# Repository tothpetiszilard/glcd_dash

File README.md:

# glcd_dash
Very old (2015) project - T6963 based GLCD dashboard for a motorcycle

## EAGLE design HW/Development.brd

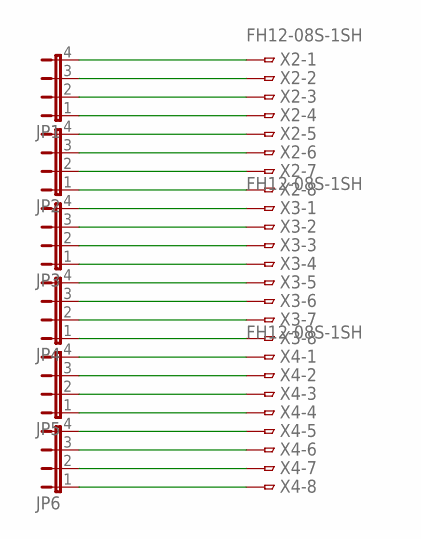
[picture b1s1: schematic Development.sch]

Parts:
JP1, JP2, JP3, JP4, JP5, JP6: JP4E; JP4
X2, X3, X4: FH12-08S-1SH

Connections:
unnamed: JP1.4, X2.1
unnamed: JP1.3, X2.2
unnamed: JP1.2, X2.3
unnamed: JP1.1, X2.4
unnamed: JP2.4, X2.5
unnamed: JP2.3, X2.6
unnamed: JP2.2, X2.7
unnamed: JP2.1, X2.8
unnamed: JP3.4, X3.1
unnamed: JP3.3, X3.2
unnamed: JP3.2, X3.3
unnamed: JP3.1, X3.4
unnamed: JP4.4, X3.5
unnamed: JP4.3, X3.6
unnamed: JP4.2, X3.7
unnamed: JP4.1, X3.8
unnamed: JP5.4, X4.1
unnamed: JP5.3, X4.2
unnamed: JP5.2, X4.3
unnamed: JP5.1, X4.4
unnamed: JP6.4, X4.5
unnamed: JP6.3, X4.6
unnamed: JP6.2, X4.7
unnamed: JP6.1, X4.8

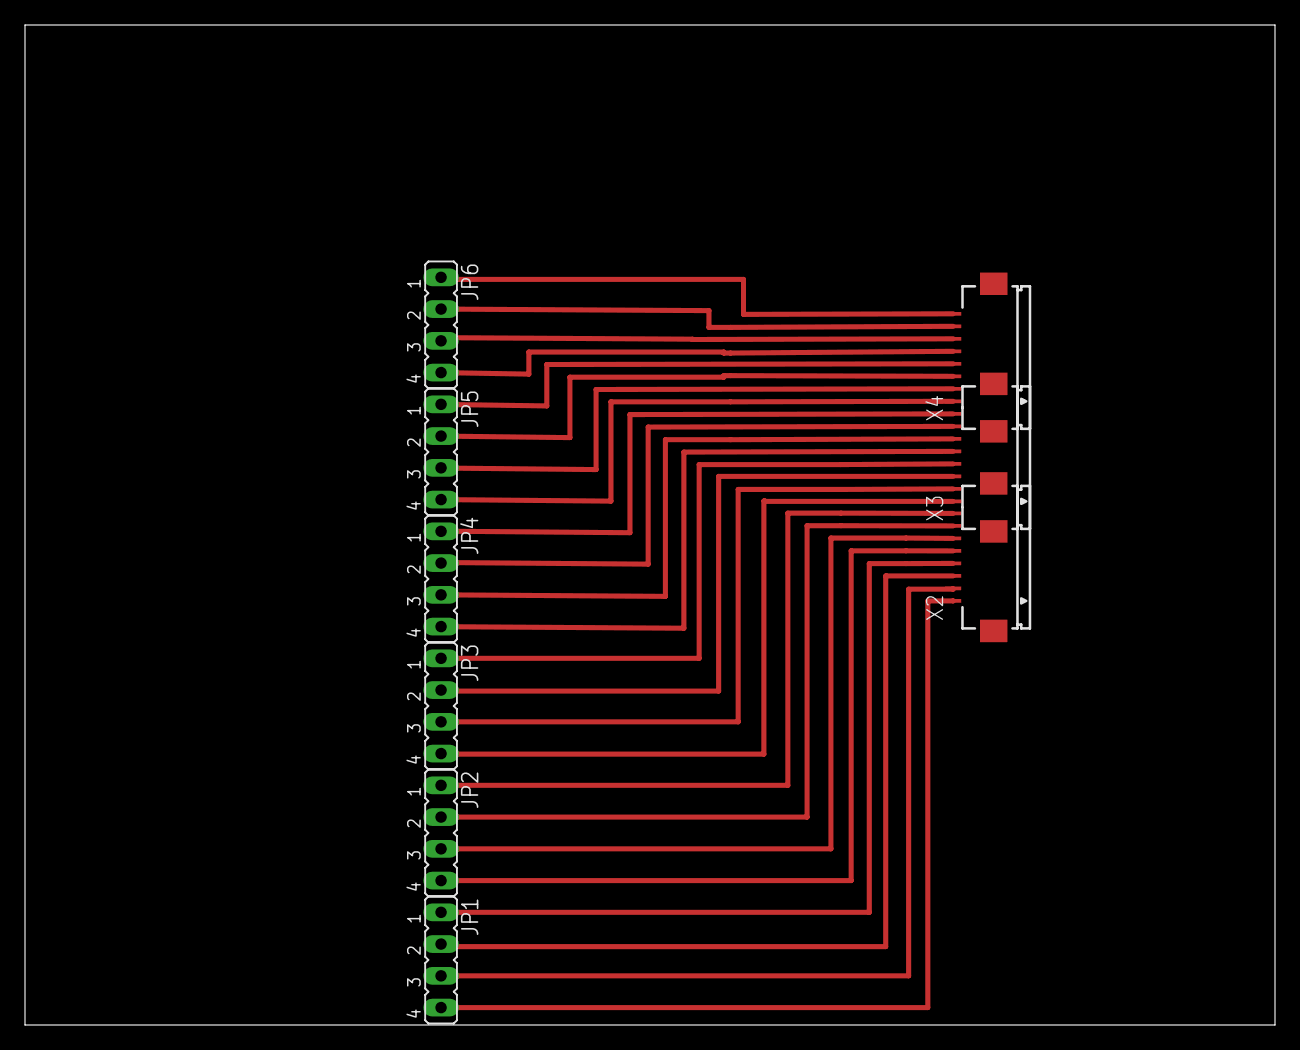
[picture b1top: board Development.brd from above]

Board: 2 copper layers, 100.0 x 80.0 mm, 9 parts (0 on the bottom side), 24 nets.

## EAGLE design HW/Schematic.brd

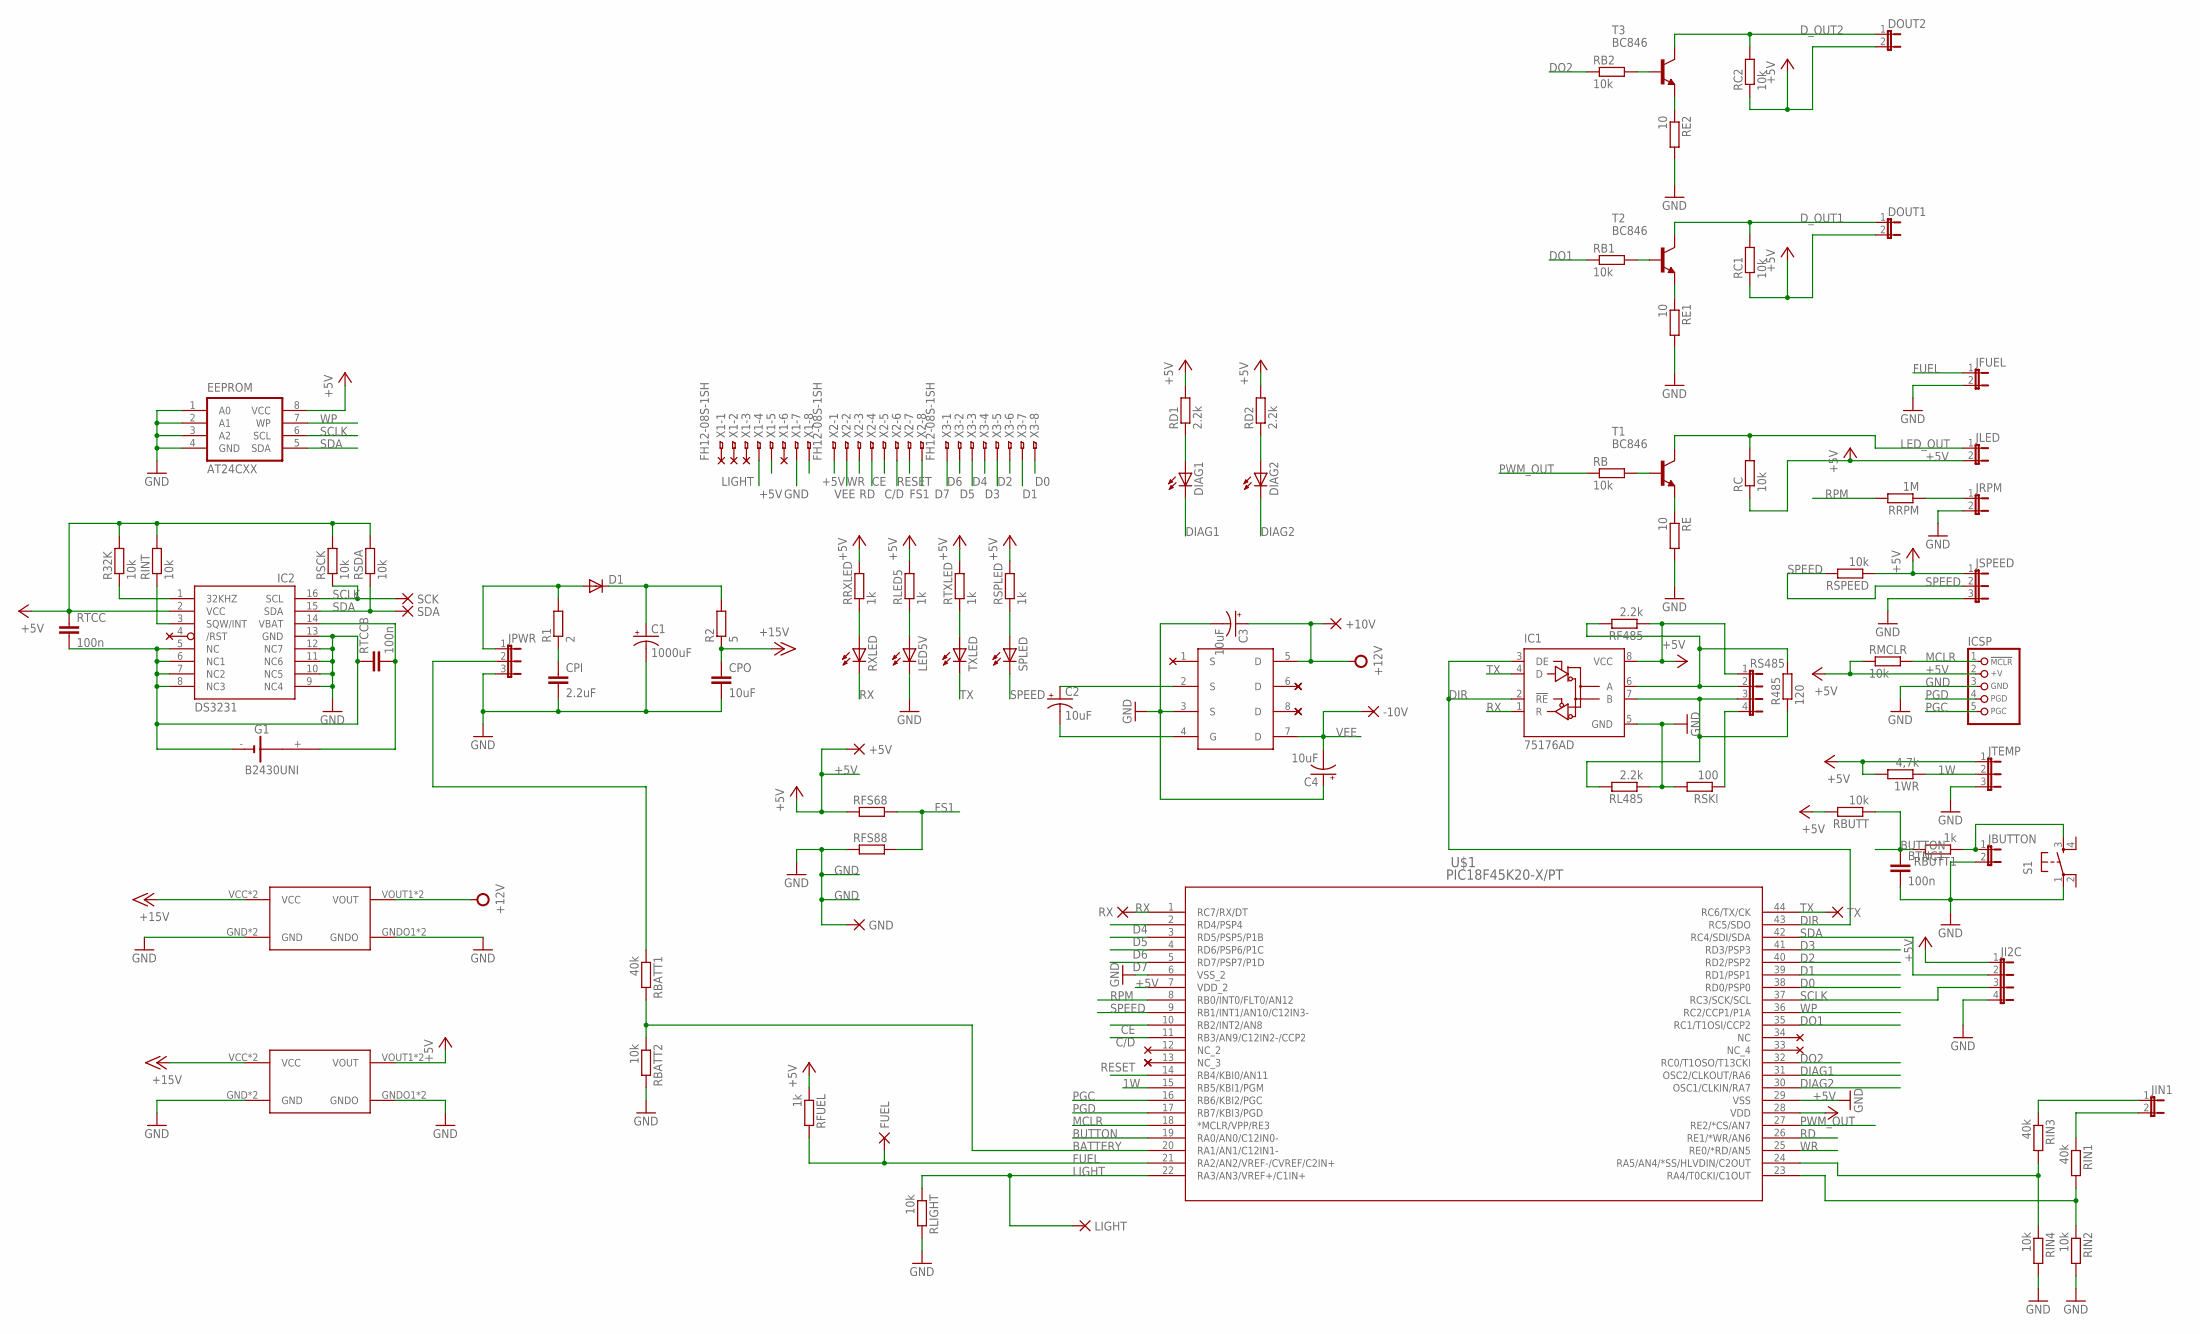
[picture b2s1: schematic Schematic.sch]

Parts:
1WR: 4,7k; R0603
+5V, +10V: PAD-SMD20R; SMD20R
-10V: PAD-SMD20R; SMD20R
BTNC1: 100n; C1206
C1: 1000uF; CPOL-RADIAL-1000UF-25V
C2, C3, C4: 10uF; EIA3216
CPI: 2.2uF; C1206
CPO: 10uF; C1206
D1: DIODE-SOD106-R; SOD106-R
DIAG1, DIAG2: LEDCHIPLED_0603; CHIPLED_0603
DOUT1, DOUT2: JP1E; JP1
EEPROM: AT24CXX; SO08-8S1
FUEL: PAD-SMD20R; SMD20R
G1: B2430UNI
GND: PAD-SMD20R; SMD20R
IC1: 75176AD; D_R-PDSO-G8
IC2: DS3231/SO; SO16W
ICSP: CON_HEADER_PRG_PIC_ICSPB; HEADER_PRG_1X05_ICSP_B
JBUTTON: JP1E; JP1
JFUEL: JP1E; JP1
JI2C: JP4E; JP4
JIN1: JP1E; JP1
JLED: JP1E; JP1
JPWR: JP2E; JP2
JRPM: JP1E; JP1
JSPEED: JP2E; JP2
JTEMP: JP2E; JP2
LED5V: LEDCHIPLED_0603; CHIPLED_0603
LIGHT: PAD-SMD20R; SMD20R
PW5, PW12: DCDC_EBAY
R1: 2; R1206
R2: 5; R1206
R32K: 10k; R0603
R485: 120; R0603
RB, RB1, RB2: 10k; R0603
RBATT1: 40k; R0603
RBATT2: 10k; R0603
RBUTT: 10k; R0603
RBUTT1: 1k; R0603
RC, RC1, RC2: 10k; R0603
RD1, RD2: 2.2k; R0603
RE, RE1, RE2: 10; R0603
RF485: 2.2k; R0603
RFS68, RFS88: RR0603; R0603
RFUEL: 1k; R0603
RIN1, RIN3: 40k; R0603
RIN2, RIN4: 10k; R0603
RINT: 10k; R0603
RL485: 2.2k; R0603
RLED5: 1k; R0603
RLIGHT: 10k; R0603
RMCLR: 10k; R0603
RRPM: 1M; R0603
RRXLED: 1k; R0603
RS485: JP4E; JP4
RSCK: 10k; R0603
RSDA: 10k; R0603
RSKI: 100; R0603
RSPEED: 10k; R0603
RSPLED: 1k; R0603
RTCC: 100n; C1206
RTCCB: 100n; C1206
RTXLED: 1k; R0603
RX: PAD-SMD20R; SMD20R
RXLED: LEDCHIPLED_0603; CHIPLED_0603
S1: TAC_SWITCHPTH; TACTILE-PTH
SCK: PAD-SMD20R; SMD20R
SDA: PAD-SMD20R; SMD20R
SPLED: LEDCHIPLED_0603; CHIPLED_0603
T1, T2, T3: BC846; SOT23
TX: PAD-SMD20R; SMD20R
TXLED: LEDCHIPLED_0603; CHIPLED_0603
U$1: PIC18F45K20-X/PT; TQFP44_MC
U$2: NDS8434; SO08
U$3, U$4, U$5, U$6, U$7, U$8, U$9, U$10, U$11, U$12, U$13, U$14, U$15, U$16, U$17: NC
X1, X2, X3: FH12-08S-1SH

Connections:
1W: 1WR.1, JTEMP.2, U$1.15 (RB5/KBI1/PGM)
+5V: 1WR.2, +5V.PAD, DOUT1.2, DOUT2.2, EEPROM.8 (VCC), IC1.8 (VCC), IC2.2 (VCC), ICSP.2 (+V), JI2C.1, JLED.2, JSPEED.1, JTEMP.1, PW5.VOUT1 (VOUT), PW5.VOUT2 (VOUT), R32K.2, RBUTT.2, RC.1, RC1.1, RC2.1, RD1.2, RD2.2, RF485.1, RFS68.1, RFUEL.1, RINT.2, RLED5.2, RMCLR.1, RRXLED.2, RS485.1, RSCK.2, RSDA.2, RSPEED.1, RSPLED.2, RTCC.1, RTXLED.2, U$1.7 (VDD_2), U$1.28 (VDD), X1.5, X2.1
+12V: +10V.PAD, C3.A (+), PW12.VOUT1 (VOUT), PW12.VOUT2 (VOUT), U$2.5 (D)
+15V: CPO.1, PW5.VCC, PW5.VCCIN (VCC), PW12.VCC, PW12.VCCIN (VCC), R2.1
BATTERY: RBATT1.2, RBATT2.1, U$1.20 (RA1/AN1/C12IN1-)
BATTERY1: RIN1.2, RIN2.1, U$1.23 (RA4/T0CKI/C1OUT)
BATTERY2: RIN3.2, RIN4.1, U$1.24 (RA5/AN4/*SS/HLVDIN/C2OUT)
BUTTON: BTNC1.1, RBUTT.1, RBUTT1.2, U$1.19 (RA0/AN0/C12IN0-)
C/D: U$1.11 (RB3/AN9/C12IN2-/CCP2), X2.6
CE: U$1.10 (RB2/INT2/AN8), X2.5
D0: U$1.38 (RD0/PSP0), X3.8
D1: U$1.39 (RD1/PSP1), X3.7
D2: U$1.40 (RD2/PSP2), X3.6
D3: U$1.41 (RD3/PSP3), X3.5
D4: U$1.2 (RD4/PSP4), X3.4
D5: U$1.3 (RD5/PSP5/P1B), X3.3
D6: U$1.4 (RD6/PSP6/P1C), X3.2
D7: U$1.5 (RD7/PSP7/P1D), X3.1
DIAG1: DIAG1.C, U$1.31 (OSC2/CLKOUT/RA6)
DIAG2: DIAG2.C, U$1.30 (OSC1/CLKIN/RA7)
DIR: IC1.2 (!RE), IC1.3 (DE), U$1.43 (RC5/SDO)
DO1: RB1.1, U$1.35 (RC1/T1OSI/CCP2)
DO2: RB2.1, U$1.32 (RC0/T1OSO/T13CKI)
D_OUT1: DOUT1.1, RC1.2, T2.3 (C)
D_OUT2: DOUT2.1, RC2.2, T3.3 (C)
FS1: RFS68.2, RFS88.2, X2.8
FUEL: FUEL.PAD, JFUEL.1, RFUEL.2, U$1.21 (RA2/AN2/VREF-/CVREF/C2IN+)
GND: BTNC1.2, C1.2 (-), C3.C (-), C4.A (+), CPI.2, CPO.2, EEPROM.1 (A0), EEPROM.2 (A1), EEPROM.3 (A2), EEPROM.4 (GND), G1.-, GND.PAD, IC1.5 (GND), IC2.5 (NC), IC2.6 (NC1), IC2.7 (NC2), IC2.8 (NC3), IC2.9 (NC4), IC2.10 (NC5), IC2.11 (NC6), IC2.12 (NC7), IC2.13 (GND), ICSP.3 (GND), JBUTTON.2, JFUEL.2, JI2C.4, JPWR.3, JRPM.2, JSPEED.3, JTEMP.3, LED5V.C, PW5.GND, PW5.GND2 (GND), PW5.GNDO1 (GNDO), PW5.GNDO2 (GNDO), PW12.GND, PW12.GND2 (GND), PW12.GNDO1 (GNDO), PW12.GNDO2 (GNDO), RBATT2.2, RE.2, RE1.2, RE2.2, RFS88.1, RIN2.2, RIN4.2, RL485.1, RLIGHT.2, RSKI.2, RTCC.2, RTCCB.1, S1.1, U$1.6 (VSS_2), U$1.29 (VSS), U$2.3 (S), X1.7, X1.8
LED_OUT: JLED.1, RC.2, T1.3 (C)
LIGHT: LIGHT.PAD, RLIGHT.1, U$1.22 (RA3/AN3/VREF+/C1IN+), X1.4
MCLR: ICSP.1 (/MCLR), RMCLR.2, U$1.18 (*MCLR/VPP/RE3)
unnamed: LED5V.A, RLED5.1
unnamed: RRXLED.1, RXLED.A
unnamed: RTXLED.1, TXLED.A
unnamed: JBUTTON.1, RBUTT1.1, S1.3
unnamed: RE.1, T1.2 (E)
unnamed: JRPM.1, RRPM.1
unnamed: RB.2, T1.1 (B)
unnamed: JPWR.2, RBATT1.1
unnamed: RE1.1, T2.2 (E)
unnamed: RB1.2, T2.1 (B)
unnamed: RE2.1, T3.2 (E)
unnamed: RB2.2, T3.1 (B)
unnamed: DIAG1.A, RD1.1
unnamed: C1.1 (+), D1.C, R2.2
unnamed: CPI.1, R1.1
unnamed: RSPLED.1, SPLED.A
unnamed: C2.A (+), U$2.2 (S)
unnamed: C2.C (-), U$2.4 (G)
unnamed: IC1.6 (A), R485.2, RF485.2, RS485.2
unnamed: IC1.7 (B), R485.1, RL485.2, RS485.3
unnamed: JIN1.2, RIN1.1
unnamed: IC2.1 (32KHZ), R32K.1
unnamed: IC2.3 (SQW/INT), RINT.1
unnamed: G1.+, IC2.14 (VBAT), RTCCB.2
unnamed: JIN1.1, RIN3.1
unnamed: D1.A, JPWR.1, R1.2
unnamed: DIAG2.A, RD2.1
unnamed: RS485.4, RSKI.1
PGC: ICSP.5 (PGC), U$1.16 (RB6/KBI2/PGC)
PGD: ICSP.4 (PGD), U$1.17 (RB7/KBI3/PGD)
PWM_OUT: RB.1, U$1.27 (RE2/*CS/AN7)
RD: U$1.26 (RE1/*WR/AN6), X2.4
RESET: U$1.14 (RB4/KBI0/AN11), X2.7
RPM: RRPM.2, U$1.8 (RB0/INT0/FLT0/AN12)
RX: IC1.1 (R), RX.PAD, RXLED.C, U$1.1 (RC7/RX/DT)
SCLK: EEPROM.6 (SCL), IC2.16 (SCL), JI2C.3, RSCK.1, SCK.PAD, U$1.37 (RC3/SCK/SCL)
SDA: EEPROM.5 (SDA), IC2.15 (SDA), JI2C.2, RSDA.1, SDA.PAD, U$1.42 (RC4/SDI/SDA)
SPEED: JSPEED.2, RSPEED.2, SPLED.C, U$1.9 (RB1/INT1/AN10/C12IN3-)
TX: IC1.4 (D), TX.PAD, TXLED.C, U$1.44 (RC6/TX/CK)
VEE: -10V.PAD, C4.C (-), U$2.7 (D), X2.2
WP: EEPROM.7 (WP), U$1.36 (RC2/CCP1/P1A)
WR: U$1.25 (RE0/*RD/AN5), X2.3

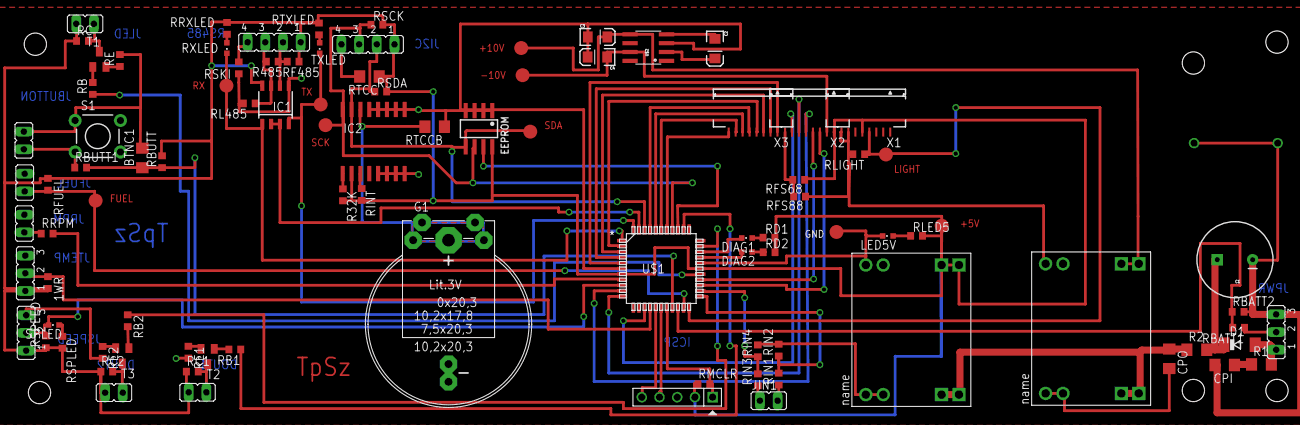
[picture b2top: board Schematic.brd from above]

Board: 2 copper layers, 111 parts (0 on the bottom side), 73 nets.

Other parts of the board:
DRILEGEND: DRILEGEND

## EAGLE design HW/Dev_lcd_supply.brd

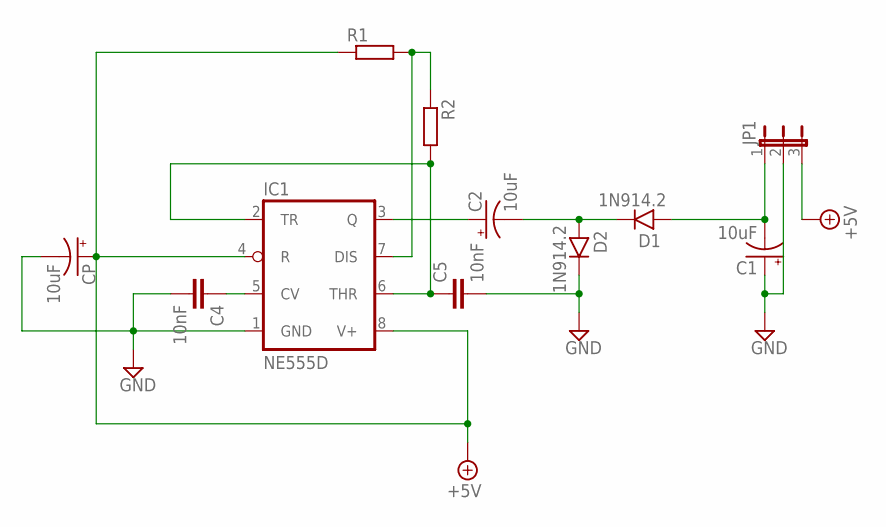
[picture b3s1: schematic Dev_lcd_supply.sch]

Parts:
C1, C2: 10uF; EIA3216
C4, C5: 10nF; 0402-CAP
CP: 10uF; EIA3216
D1, D2: 1N914.2; DO35-2
IC1: NE555D; SO08
JP1: JP2E; JP2
R1, R2: RR0603; R0603

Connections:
+5V: CP.A (+), IC1.4 (R), IC1.8 (V+), JP1.3, R1.1
GND: C1.A (+), C4.2, C5.2, CP.C (-), D2.C, IC1.1 (GND), JP1.2
unnamed: C2.A (+), IC1.3 (Q)
unnamed: C2.C (-), D1.C, D2.A
unnamed: C1.C (-), D1.A, JP1.1
unnamed: C4.1, IC1.5 (CV)
unnamed: C5.1, IC1.2 (TR), IC1.6 (THR), R2.2
unnamed: IC1.7 (DIS), R1.2, R2.1

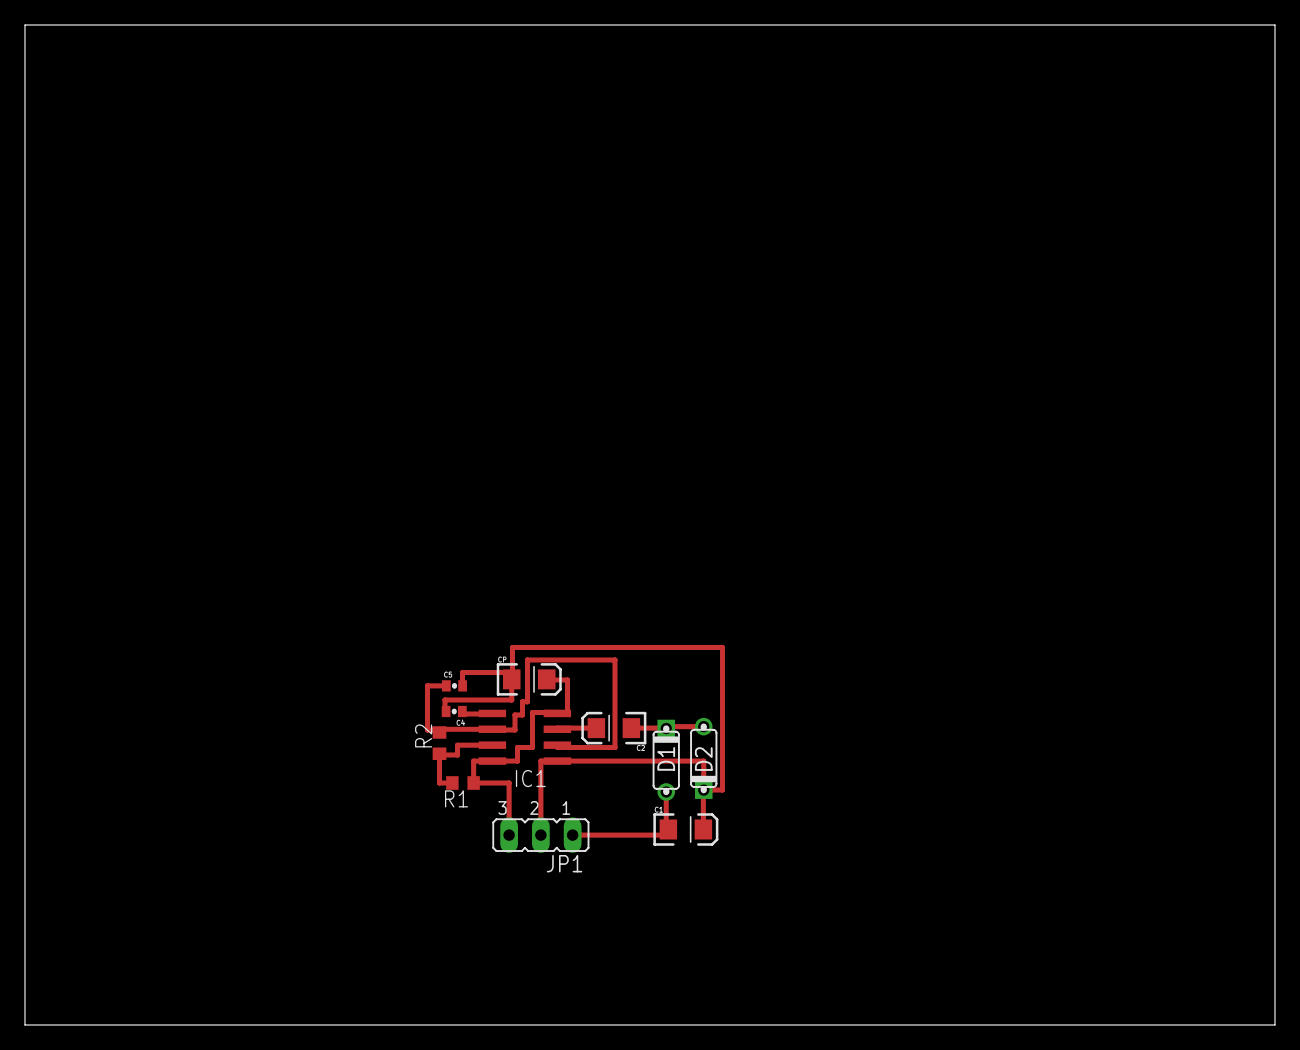
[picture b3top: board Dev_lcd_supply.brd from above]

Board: 2 copper layers, 100.0 x 80.0 mm, 11 parts (0 on the bottom side), 8 nets.

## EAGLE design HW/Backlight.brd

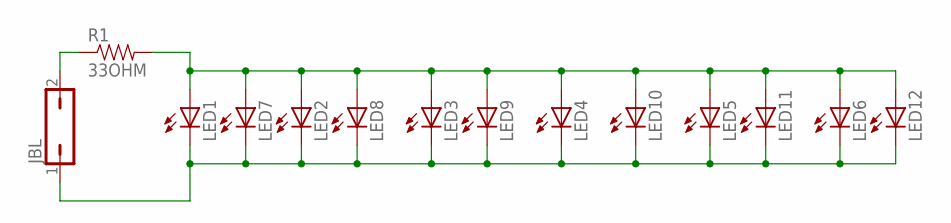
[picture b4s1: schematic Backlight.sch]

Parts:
JBL: JP1Q; JP1
LED1, LED2, LED3, LED4, LED5, LED6, LED7, LED8, LED9, LED10, LED11, LED12: LEDCHIP-LED0603; CHIP-LED0603
R1: 33OHM; 0603

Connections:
unnamed: LED1.A, LED2.A, LED3.A, LED4.A, LED5.A, LED6.A, LED7.A, LED8.A, LED9.A, LED10.A, LED11.A, LED12.A, R1.2
unnamed: JBL.1, LED1.C, LED2.C, LED3.C, LED4.C, LED5.C, LED6.C, LED7.C, LED8.C, LED9.C, LED10.C, LED11.C, LED12.C
unnamed: JBL.2, R1.1

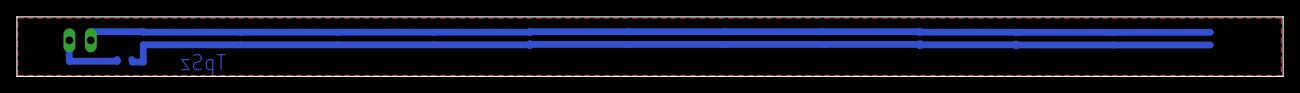
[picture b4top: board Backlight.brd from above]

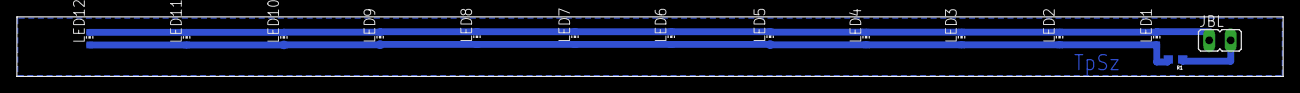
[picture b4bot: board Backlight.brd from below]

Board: 2 copper layers, 150.0 x 7.0 mm, 14 parts (14 on the bottom side), 3 nets.

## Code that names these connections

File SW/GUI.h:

/* 
 * File:   GUI.h
 * Author: Tóthpeti Szilárd
 *
 * Created on 2015. május 7., 15:27
 */
#include <xc.h>
#include <stdio.h>

// -------- GUI define -------------------------------------------------------------------------
#define longpress   250 // *2,04 msec
#define shortpress  20 // *2,04 msec

#define byte unsigned char

#define softtimermax    200

#define DOUT_1  LATCbits.LATC0
#define DOUT_2  LATCbits.LATC1
#define DIAG1   LATAbits.LATA6
#define DIAG2   LATAbits.LATA7

// -------------- GUI ---------------------------------------------------------------------------------
void dsp_time   ();
void dsp_mileage();
void home();
void menu();
void sleep();
void wake();
void dsp_distance();
void dsp_rpm(unsigned int val);
void dsp_rpmbar(unsigned int val);
void dsp_dstemp(byte id);
void dsp_atemp();
void dsp_avgspeed();
void dsp_maxspeed();
void dsp_optime();
void dsp_dayofweek();
void dsp_battery();
void config();
void changeTime(byte x ,byte y);
void setBacklight();
void listTemp();
void setTemp(byte id);
void autoBright();
void autoHeadlight();
void options();

void readConfig();
unsigned long int readOptime();
unsigned long int readMileage ();
void readDS();
unsigned int readDistance();
unsigned int readAvgdistance();
unsigned int readSptime();

void saveConfig();
void saveDS();
/*void saveOptime();
void saveMileage();

void saveAvg ();
void saveDistance();*/
//void saveAll();

unsigned char dec2bcd(unsigned char num);
unsigned char bcd2dec(unsigned char num);

unsigned char ahhist=10;
unsigned char ahdone=0;
volatile unsigned int speed=0; // speed signal counter
unsigned char speed_val=0; // Current speed value
unsigned char ahspeed=70; // Speed when headlights ON
volatile unsigned int rpm=0; // rpm signal? (zcd) counter
unsigned char rpm_val=0; // Current RPM data/120
volatile unsigned int signalcount=0; // Distance in meters below 1 km
unsigned long mileage=0; // all kms in km
unsigned int distance=0; // napi km
unsigned int avgdistance=0; // átlagszámításhoz km
unsigned char max_speed=0; // Ennyivel mentünk eddig max
float avg_speed=0;
volatile unsigned long int sptime=0; // mozgassal eltelt ido (fél mp)
volatile unsigned long int uzemora=0; // összes üzemóra
volatile byte button_cmd=0; // 0 = Not pressed, 1 short pressed , 2 long pressed, sw cleared
unsigned int brightness=600;
byte CONFIG=0; // 0. bit = AutoLight; 1.bit = ;
volatile byte softtimer=0;
byte ahtimer=0;
unsigned int battery=0;
unsigned int light=0;
unsigned int ahlight=30; // Lightness when Headlights ON
const unsigned char HOMEMAX=2;
 
#ifndef GUI_H
#define	GUI_H

#ifdef	__cplusplus
extern "C" {
#endif




#ifdef	__cplusplus
}
#endif

#endif	/* GUI_H */

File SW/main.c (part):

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#pragma config FOSC = INTOSC    // Oscillator Selection Bits (INTOSC oscillator: I/O function on CLKIN pin)
#pragma config WDTE = OFF       // Watchdog Timer Enable (WDT disabled)
#pragma config PWRTE = ON       // Power-up Timer Enable (PWRT enabled)
#pragma config MCLRE = ON       // MCLR Pin Function Select (MCLR/VPP pin function is MCLR)
#pragma config CP = OFF         // Flash Program Memory Code Protection (Program memory code protection is disabled)
#pragma config BOREN = ON       // Brown-out Reset Enable (Brown-out Reset enabled)
#pragma config CLKOUTEN = OFF   // Clock Out Enable (CLKOUT function is disabled. I/O or oscillator function on the CLKOUT pin)
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{
    speed_val=speed; // Gives speed data ( 942 mm/s )
    rpm_val=rpm; // Gives rpm in RPM
    rpm=0;
    speed=0;
    if (speed_val) sptime++; // Ha nem 0 a sebesség, ido növelése
    if (rpm_val) uzemora++; // Ha megy a gépállat, no az üzemóra
    TMR1=tmr1preload;
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        TMR4=0;
        T4CONbits.TMR4ON=1;
    }
    IOCAFbits.IOCAF0 = 0; // RA0 (Button) Int Flag clear
}


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    sptime=readSptime();
    readDS();
    //check_Ignition();
    IOCANbits.IOCAN1=1; // Battery Input Falling edge Int
    home();

}
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void Init_Interrupts ()
{
    INTCONbits.GIE=0;
    TRISBbits.TRISB1=1; // Speed pin Input
    TRISAbits.TRISA6=0; // Diag led 1 out
    TRISAbits.TRISA7=0; // Diag led 2 out
    ANSELBbits.ANSB1=0; // Speed pin Digital Input
    TRISCbits.TRISC0=0; // Digital out 1
    TRISCbits.TRISC1=0; // Digital out 1
    INTCON=0b01011000; // Global, Periferial, TMR0, INT0, PC Int, ...Flags
    PIE3bits.ZCDIE=1; // ZCD Interrupt (RPM Signal?)
    OPTION_REGbits.INTEDG=0; // Falling Edge Int0 // Speed Hall Sensor (10k +5V)
    INTCONbits.INTE=1;
    ANSELAbits.ANSA0=0; // A0 Digital In // Button
    TRISAbits.TRISA0=1; // A0 Input // Button
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
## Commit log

2022-10-21 Backup of a very old project from 2015

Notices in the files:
parts and their libraries:
SparkFun-Resistors: Licensing: Creative Commons ShareAlike 4.0 International - https://creativecommons.org/licenses/by-sa/4.0
dpads: Copyright (C) 2004, Bob Starr (bobstarr@mindspring.com)
memory-atmel: Copyright (C) 2008, Bob Starr
